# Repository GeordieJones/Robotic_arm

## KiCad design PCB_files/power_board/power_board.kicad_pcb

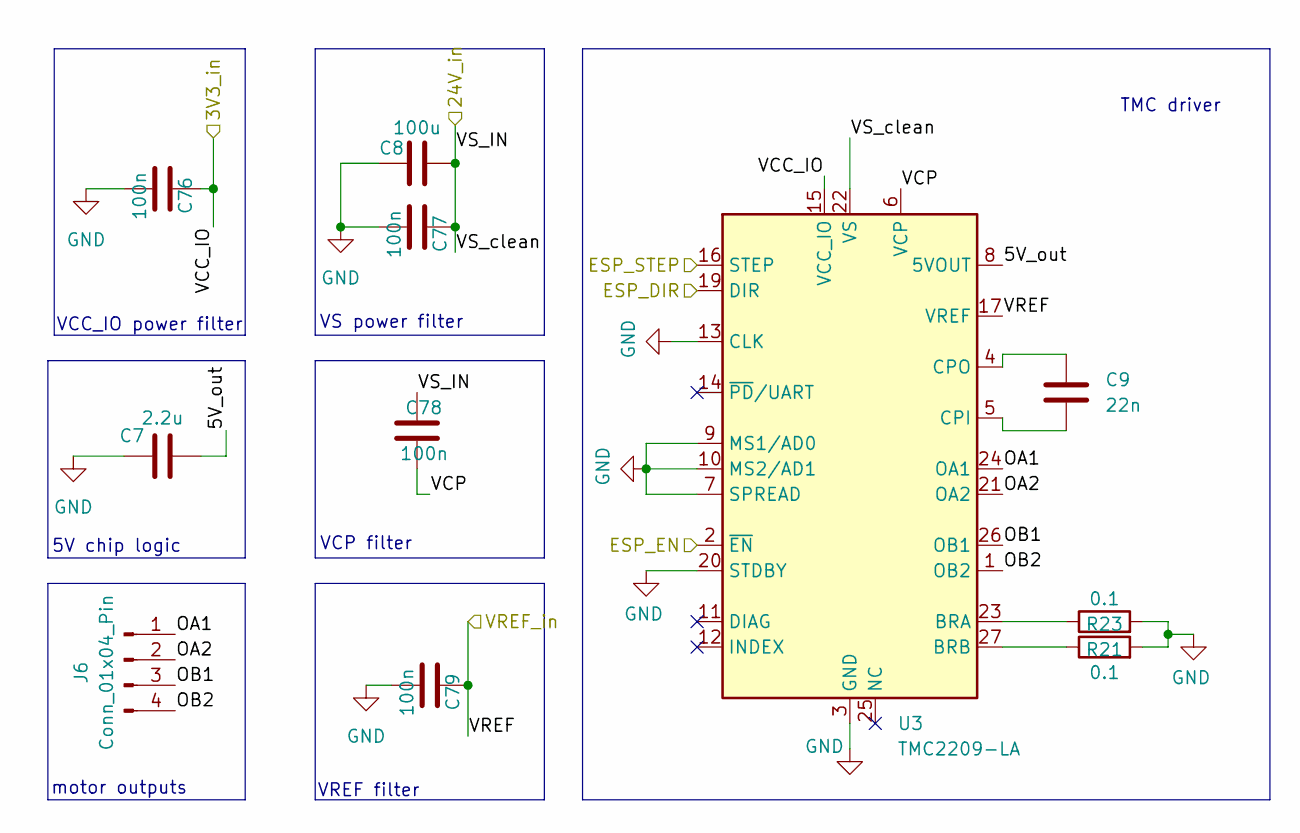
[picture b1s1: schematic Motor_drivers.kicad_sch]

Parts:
C7: 2.2u; C_0603_1608Metric
C8: 100u; CP_Radial_D6.3mm_P2.50mm
C9: 22n; C_0603_1608Metric
C76: 100n; C_0402_1005Metric; part samsung CL05B104KP5NNNC
C77, C78, C79: 100n; C_0603_1608Metric; part KEMET C0603C104K5RACTU
J6: Conn_01x04_Pin; JST_XA_B04B-XASK-1-A_1x04_P2.50mm_Vertical
R21, R23: 0.1; R_0805_2012Metric
U3: TMC2209-LA; VQFN-28-1EP_5x5mm_P0.5mm_EP3.7x3.7mm_ThermalVias

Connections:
3V3: C76.1, U3.15 (VCC_IO); also elsewhere on the board
24V: C8.1, C77.1, C78.1, U3.22 (VS), U3.28 (VS); also elsewhere on the board
/2_DIR: U3.19 (DIR); also elsewhere on the board
/2_STEP: U3.16 (STEP); also elsewhere on the board
/EN: U3.2 (~EN); also elsewhere on the board
/Motor_driver2/5V_out: C7.2, U3.8 (5VOUT)
/Motor_driver2/OA1: J6.1, U3.24 (OA1)
/Motor_driver2/OA2: J6.2, U3.21 (OA2)
/Motor_driver2/OB1: J6.3, U3.26 (OB1)
/Motor_driver2/OB2: J6.4, U3.1 (OB2)
/Motor_driver2/VCP: C78.2, U3.6 (VCP)
/VREF_ART2: C79.1, U3.17 (VREF); also elsewhere on the board
GND: C7.1, C8.2, C76.2, C77.2, C79.2, R21.2, R23.2, U3.3 (GND), U3.7 (SPREAD), U3.9 (MS1/AD0), U3.10 (MS2/AD1), U3.13 (CLK), U3.18 (GND), U3.20 (STDBY), U3.29 (GND); also elsewhere on the board
unnamed: R23.1, U3.23 (BRA)
unnamed: R21.1, U3.27 (BRB)
unnamed: C9.2, U3.5 (CPI)
unnamed: C9.1, U3.4 (CPO)

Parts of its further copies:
C4, C10, C13, C16, C19, C22: 2.2u; C_0603_1608Metric
C5, C11, C14, C17, C20, C23: 100u; CP_Radial_D6.3mm_P2.50mm
C6, C12, C15, C18, C21, C24: 22n; C_0603_1608Metric
C71, C80, C84, C91, C103, C107: 100n; C_0402_1005Metric; part samsung CL05B104KP5NNNC
C72, C73, C74, C81, C82, C83, C85, C86, C88, C97, C101, C102, C104, C105, C106, C108, C109, C110: 100n; C_0603_1608Metric; part KEMET C0603C104K5RACTU
J5, J8, J10, J11, J12, J13: Conn_01x04_Pin; JST_XA_B04B-XASK-1-A_1x04_P2.50mm_Vertical
R24, R25, R26, R27, R28, R29, R30, R36, R37, R38, R39, R40: 0.1; R_0805_2012Metric
U2, U4, U5, U6, U7, U10: TMC2209-LA; VQFN-28-1EP_5x5mm_P0.5mm_EP3.7x3.7mm_ThermalVias

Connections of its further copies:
3V3: C71.1, C80.1, C84.1, C91.1, C103.1, C107.1, U2.15 (VCC_IO), U4.15 (VCC_IO), U5.15 (VCC_IO), U6.15 (VCC_IO), U7.15 (VCC_IO), U10.15 (VCC_IO); also elsewhere on the board
24V: C5.1, C11.1, C14.1, C17.1, C20.1, C23.1, C72.1, C73.1, C81.1, C82.1, C85.1, C86.1, C97.1, C101.1, C104.1, C105.1, C108.1, C109.1, U2.22 (VS), U2.28 (VS), U4.22 (VS), U4.28 (VS), U5.22 (VS), U5.28 (VS), U6.22 (VS), U6.28 (VS), U7.22 (VS), U7.28 (VS), U10.22 (VS), U10.28 (VS); also elsewhere on the board
/1_DIR: U2.19 (DIR); also elsewhere on the board
/1_STEP: U2.16 (STEP); also elsewhere on the board
/3_DIR: U4.19 (DIR); also elsewhere on the board
/3_STEP: U4.16 (STEP); also elsewhere on the board
/4_DIR: U5.19 (DIR); also elsewhere on the board
/4_STEP: U5.16 (STEP); also elsewhere on the board
/5_DIR: U6.19 (DIR); also elsewhere on the board
/5_STEP: U6.16 (STEP); also elsewhere on the board
/6_DIR: U7.19 (DIR); also elsewhere on the board
/6_STEP: U7.16 (STEP); also elsewhere on the board
/7_DIR: U10.19 (DIR); also elsewhere on the board
/7_STEP: U10.16 (STEP); also elsewhere on the board
/EN: U2.2 (~EN), U4.2 (~EN), U5.2 (~EN), U6.2 (~EN), U7.2 (~EN), U10.2 (~EN); also elsewhere on the board
/Motor_driver1/5V_out: C4.2, U2.8 (5VOUT)
/Motor_driver1/OA1: J5.1, U2.24 (OA1)
/Motor_driver1/OA2: J5.2, U2.21 (OA2)
/Motor_driver1/OB1: J5.3, U2.26 (OB1)
/Motor_driver1/OB2: J5.4, U2.1 (OB2)
/Motor_driver1/VCP: C73.2, U2.6 (VCP)
/Motor_driver3/5V_out: C10.2, U4.8 (5VOUT)
/Motor_driver3/OA1: J8.1, U4.24 (OA1)
/Motor_driver3/OA2: J8.2, U4.21 (OA2)
/Motor_driver3/OB1: J8.3, U4.26 (OB1)
/Motor_driver3/OB2: J8.4, U4.1 (OB2)
/Motor_driver3/VCP: C82.2, U4.6 (VCP)
/Motor_driver4/5V_out: C13.2, U5.8 (5VOUT)
/Motor_driver4/OA1: J10.1, U5.24 (OA1)
/Motor_driver4/OA2: J10.2, U5.21 (OA2)
/Motor_driver4/OB1: J10.3, U5.26 (OB1)
/Motor_driver4/OB2: J10.4, U5.1 (OB2)
/Motor_driver4/VCP: C86.2, U5.6 (VCP)
/Motor_driver5/5V_out: C16.2, U6.8 (5VOUT)
/Motor_driver5/OA1: J11.1, U6.24 (OA1)
/Motor_driver5/OA2: J11.2, U6.21 (OA2)
/Motor_driver5/OB1: J11.3, U6.26 (OB1)
/Motor_driver5/OB2: J11.4, U6.1 (OB2)
/Motor_driver5/VCP: C101.2, U6.6 (VCP)
/Motor_driver6/5V_out: C19.2, U7.8 (5VOUT)
/Motor_driver6/OA1: J12.1, U7.24 (OA1)
/Motor_driver6/OA2: J12.2, U7.21 (OA2)
/Motor_driver6/OB1: J12.3, U7.26 (OB1)
/Motor_driver6/OB2: J12.4, U7.1 (OB2)
/Motor_driver6/VCP: C105.2, U7.6 (VCP)
/Motor_driver7/5V_out: C22.2, U10.8 (5VOUT)
/Motor_driver7/OA1: J13.1, U10.24 (OA1)
/Motor_driver7/OA2: J13.2, U10.21 (OA2)
/Motor_driver7/OB1: J13.3, U10.26 (OB1)
/Motor_driver7/OB2: J13.4, U10.1 (OB2)
/Motor_driver7/VCP: C109.2, U10.6 (VCP)
/VREF_ART1: C74.1, U2.17 (VREF); also elsewhere on the board
/VREF_ART2: C83.1, U4.17 (VREF); also elsewhere on the board
/VREF_ART3: C88.1, C102.1, C106.1, C110.1, U5.17 (VREF), U6.17 (VREF), U7.17 (VREF), U10.17 (VREF); also elsewhere on the board
GND: C4.1, C5.2, C10.1, C11.2, C13.1, C14.2, C16.1, C17.2, C19.1, C20.2, C22.1, C23.2, C71.2, C72.2, C74.2, C80.2, C81.2, C83.2, C84.2, C85.2, C88.2, C91.2, C97.2, C102.2, C103.2, C104.2, C106.2, C107.2, C108.2, C110.2, R24.2, R25.2, R26.2, R27.2, R28.2, R29.2, R30.2, R36.2, R37.2, R38.2, R39.2, R40.2, U2.3 (GND), U2.7 (SPREAD), U2.9 (MS1/AD0), U2.10 (MS2/AD1), U2.13 (CLK), U2.18 (GND), U2.20 (STDBY), U2.29 (GND), U4.3 (GND), U4.7 (SPREAD), U4.9 (MS1/AD0), U4.10 (MS2/AD1), U4.13 (CLK), U4.18 (GND), U4.20 (STDBY), U4.29 (GND), U5.3 (GND), U5.7 (SPREAD), U5.9 (MS1/AD0), U5.10 (MS2/AD1), U5.13 (CLK), U5.18 (GND), U5.20 (STDBY), U5.29 (GND), U6.3 (GND), U6.7 (SPREAD), U6.9 (MS1/AD0), U6.10 (MS2/AD1), U6.13 (CLK), U6.18 (GND), U6.20 (STDBY), U6.29 (GND), U7.3 (GND), U7.7 (SPREAD), U7.9 (MS1/AD0), U7.10 (MS2/AD1), U7.13 (CLK), U7.18 (GND), U7.20 (STDBY), U7.29 (GND), U10.3 (GND), U10.7 (SPREAD), U10.9 (MS1/AD0), U10.10 (MS2/AD1), U10.13 (CLK), U10.18 (GND), U10.20 (STDBY), U10.29 (GND); also elsewhere on the board
unnamed: R25.1, U2.23 (BRA)
unnamed: R24.1, U2.27 (BRB)
unnamed: C6.2, U2.5 (CPI)
unnamed: C6.1, U2.4 (CPO)
unnamed: R27.1, U4.23 (BRA)
unnamed: R26.1, U4.27 (BRB)
unnamed: C12.2, U4.5 (CPI)
unnamed: C12.1, U4.4 (CPO)
unnamed: R28.1, U5.23 (BRA)
unnamed: R37.1, U5.27 (BRB)
unnamed: C15.2, U5.5 (CPI)
unnamed: C15.1, U5.4 (CPO)
unnamed: R29.1, U6.23 (BRA)
unnamed: R38.1, U6.27 (BRB)
unnamed: C18.2, U6.5 (CPI)
unnamed: C18.1, U6.4 (CPO)
unnamed: R30.1, U7.23 (BRA)
unnamed: R39.1, U7.27 (BRB)
unnamed: C21.2, U7.5 (CPI)
unnamed: C21.1, U7.4 (CPO)
unnamed: R36.1, U10.23 (BRA)
unnamed: R40.1, U10.27 (BRB)
unnamed: C24.2, U10.5 (CPI)
unnamed: C24.1, U10.4 (CPO)

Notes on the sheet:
VS power filter
VCP filter
VREF filter
TMC driver
VCC_IO power filter
motor outputs
5V chip logic

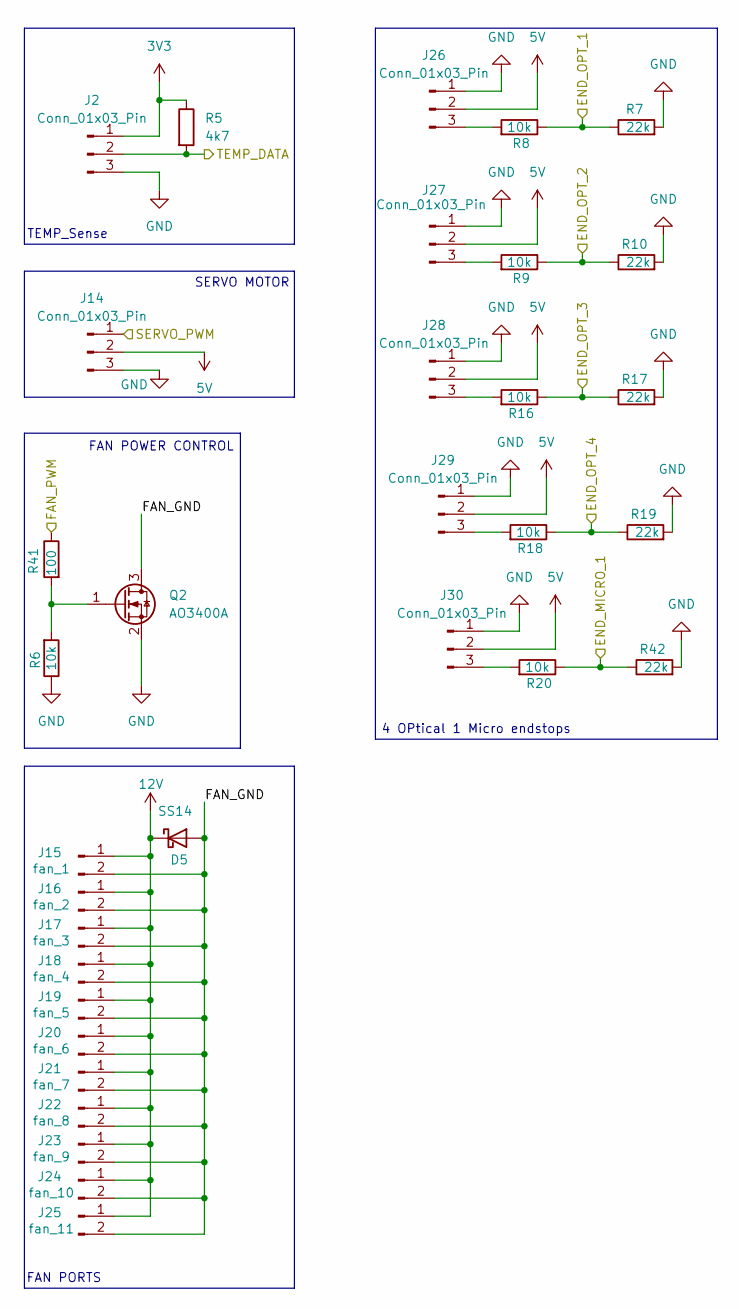
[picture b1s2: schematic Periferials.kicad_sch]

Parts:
D5: SS14; D_SMA
J2, J26, J27, J28, J29, J30: Conn_01x03_Pin; JST_XH_B3B-XH-A_1x03_P2.50mm_Vertical
J14: Conn_01x03_Pin; PinHeader_1x03_P2.54mm_Vertical
J15: fan_1; PinSocket_1x02_P2.54mm_Vertical
J16: fan_2; PinSocket_1x02_P2.54mm_Vertical
J17: fan_3; PinSocket_1x02_P2.54mm_Vertical
J18: fan_4; PinSocket_1x02_P2.54mm_Vertical
J19: fan_5; PinSocket_1x02_P2.54mm_Vertical
J20: fan_6; PinSocket_1x02_P2.54mm_Vertical
J21: fan_7; PinSocket_1x02_P2.54mm_Vertical
J22: fan_8; PinSocket_1x02_P2.54mm_Vertical
J23: fan_9; PinSocket_1x02_P2.54mm_Vertical
J24: fan_10; PinSocket_1x02_P2.54mm_Vertical
J25: fan_11; PinSocket_1x02_P2.54mm_Vertical
Q2: AO3400A; SOT-23
R5: 4k7; R_0402_1005Metric
R6, R8, R9, R16, R18, R20: 10k; R_1206_3216Metric
R7, R10, R17, R19, R42: 22k; R_0603_1608Metric
R41: 100; R_0402_1005Metric; part YAGEO RC0402FR-07100RL

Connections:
3V3: J2.1, R5.1; also elsewhere on the board
5V: J14.2, J26.2, J27.2, J28.2, J29.2, J30.2; also elsewhere on the board
12V: D5.1 (K), J15.1, J16.1, J17.1, J18.1, J19.1, J20.1, J21.1, J22.1, J23.1, J24.1, J25.1; also elsewhere on the board
/FAN_PWM: R41.1; also elsewhere on the board
/MICRO_END1: R20.1, R42.1; also elsewhere on the board
/OPT_END1: R7.1, R8.1; also elsewhere on the board
/OPT_END2: R9.1, R10.1; also elsewhere on the board
/OPT_END3: R16.1, R17.1; also elsewhere on the board
/OPT_END4: R18.1, R19.1; also elsewhere on the board
/Periferials/FAN_GND: D5.2 (A), J15.2, J16.2, J17.2, J18.2, J19.2, J20.2, J21.2, J22.2, J23.2, J24.2, J25.2, Q2.3 (D)
/SERVO_PWM: J14.1; also elsewhere on the board
/TEMP_DATA: J2.2, R5.2; also elsewhere on the board
GND: J2.3, J14.3, J26.1, J27.1, J28.1, J29.1, J30.1, Q2.2 (S), R6.1, R7.2, R10.2, R17.2, R19.2, R42.2; also elsewhere on the board
unnamed: J26.3, R8.2
unnamed: J27.3, R9.2
unnamed: J28.3, R16.2
unnamed: J29.3, R18.2
unnamed: J30.3, R20.2
unnamed: Q2.1 (G), R6.2, R41.2

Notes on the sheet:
FAN PORTS
FAN POWER CONTROL
SERVO MOTOR
TEMP_Sense
4 OPtical 1 Micro endstops

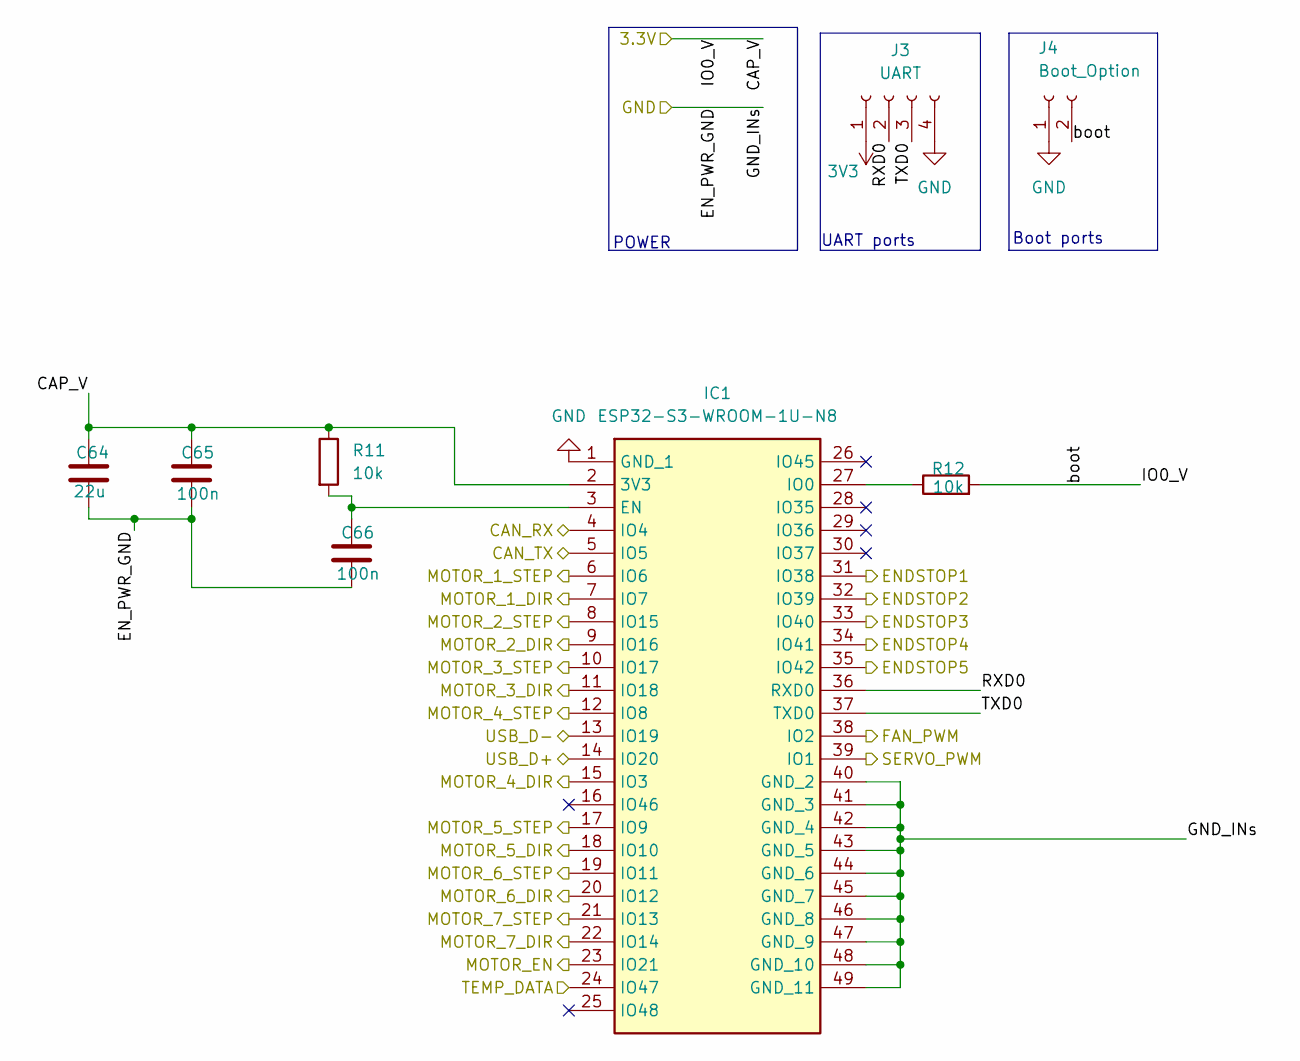
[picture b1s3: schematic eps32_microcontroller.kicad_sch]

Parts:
C64: 22u; C_0402_1005Metric; part Murata Electronics GRM158R61A226ME15D
C65, C66: 100n; C_0402_1005Metric; part samsung CL05B104KP5NNNC
IC1: ESP32-S3-WROOM-1U-N8; ESP32S3WROOM1UN8; Manufacturer_Part_Number ESP32-S3-WROOM-1U-N8; Mouser Part Number 356-ESP32S3WROOM1UN8
J3: UART; PinSocket_1x04_P2.54mm_Vertical
J4: Boot_Option; PinSocket_1x02_P2.00mm_Vertical
R11, R12: 10k; R_0402_1005Metric; part number Samsung Electro-Mechanics RC1005F103CS

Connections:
3V3: C64.1, C65.1, IC1.2 (3V3), J3.1, J4.2, R11.1, R12.2; also elsewhere on the board
/1_DIR: IC1.7 (IO7); also elsewhere on the board
/1_STEP: IC1.6 (IO6); also elsewhere on the board
/2_DIR: IC1.9 (IO16); also elsewhere on the board
/2_STEP: IC1.8 (IO15); also elsewhere on the board
/3_DIR: IC1.11 (IO18); also elsewhere on the board
/3_STEP: IC1.10 (IO17); also elsewhere on the board
/4_DIR: IC1.15 (IO3); also elsewhere on the board
/4_STEP: IC1.12 (IO8); also elsewhere on the board
/5_DIR: IC1.18 (IO10); also elsewhere on the board
/5_STEP: IC1.17 (IO9); also elsewhere on the board
/6_DIR: IC1.20 (IO12); also elsewhere on the board
/6_STEP: IC1.19 (IO11); also elsewhere on the board
/7_DIR: IC1.22 (IO14); also elsewhere on the board
/7_STEP: IC1.21 (IO13); also elsewhere on the board
/C_RX: IC1.4 (IO4); also elsewhere on the board
/C_TX: IC1.5 (IO5); also elsewhere on the board
/EN: IC1.23 (IO21); also elsewhere on the board
/FAN_PWM: IC1.38 (IO2); also elsewhere on the board
/MICRO_END1: IC1.35 (IO42); also elsewhere on the board
/OPT_END1: IC1.31 (IO38); also elsewhere on the board
/OPT_END2: IC1.32 (IO39); also elsewhere on the board
/OPT_END3: IC1.33 (IO40); also elsewhere on the board
/OPT_END4: IC1.34 (IO41); also elsewhere on the board
/SERVO_PWM: IC1.39 (IO1); also elsewhere on the board
/TEMP_DATA: IC1.24 (IO47); also elsewhere on the board
/USB+: IC1.14 (IO20); also elsewhere on the board
/USB-: IC1.13 (IO19); also elsewhere on the board
/esp32_microcontroller/RXD0: IC1.36 (RXD0), J3.2
/esp32_microcontroller/TXD0: IC1.37 (TXD0), J3.3
GND: C64.2, C65.2, C66.2, IC1.1 (GND_1), IC1.40 (GND_2), IC1.41 (GND_3), IC1.42 (GND_4), IC1.43 (GND_5), IC1.44 (GND_6), IC1.45 (GND_7), IC1.46 (GND_8), IC1.47 (GND_9), IC1.48 (GND_10), IC1.49 (GND_11), J3.4, J4.1; also elsewhere on the board
unnamed: C66.1, IC1.3 (EN), R11.2
unnamed: IC1.27 (IO0), R12.1

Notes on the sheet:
UART ports
POWER
Boot ports

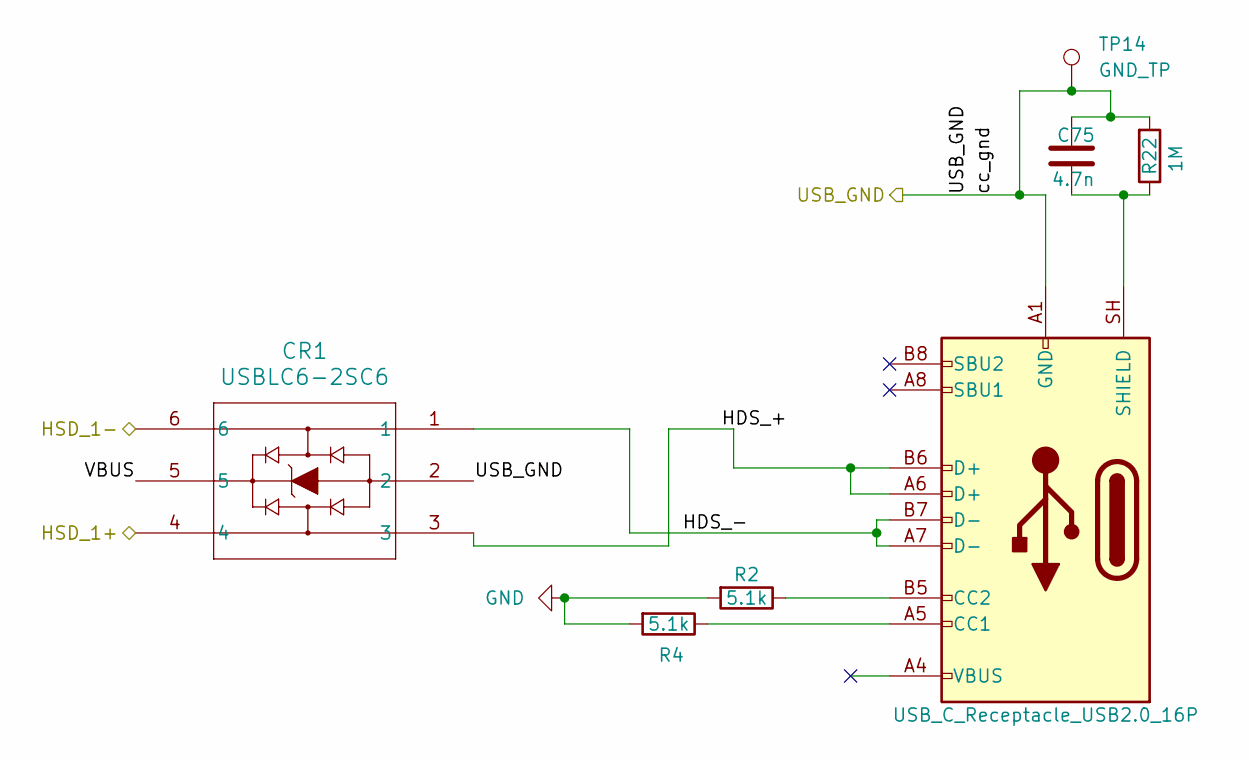
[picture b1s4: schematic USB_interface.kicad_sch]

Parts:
C75: 4.7n; LED_0603_1608Metric
CR1: USBLC6-2SC6; SOT23-6L_STM-M
J7: USB_C_Receptacle_USB2.0_16P; USB_C_Receptacle_GCT_USB4105-xx-A_16P_TopMnt_Horizontal; part USB4105-GF-A
R2, R4: 5.1k; R_0402_1005Metric
R22: 1M; R_0402_1005Metric; part number YAGEO RC0402FR-071ML
TP14: GND_TP; Pin_D1.0mm_L10.0mm

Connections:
/USB+: CR1.4; also elsewhere on the board
/USB-: CR1.6; also elsewhere on the board
/USB_interface/HDS_+: CR1.3, J7.A6 (D+), J7.B6 (D+)
/USB_interface/HDS_-: CR1.1, J7.A7 (D-), J7.B7 (D-)
/USB_interface/VBUS: CR1.5
GND: C75.1, CR1.2, J7.A1 (GND), J7.A12 (GND), J7.B1 (GND), J7.B12 (GND), R2.2, R4.2, R22.2, TP14.1 (1_1); also elsewhere on the board
unnamed: J7.A5 (CC1), R4.1
unnamed: J7.B5 (CC2), R2.1
unnamed: C75.2, J7.SH (SHIELD), R22.1

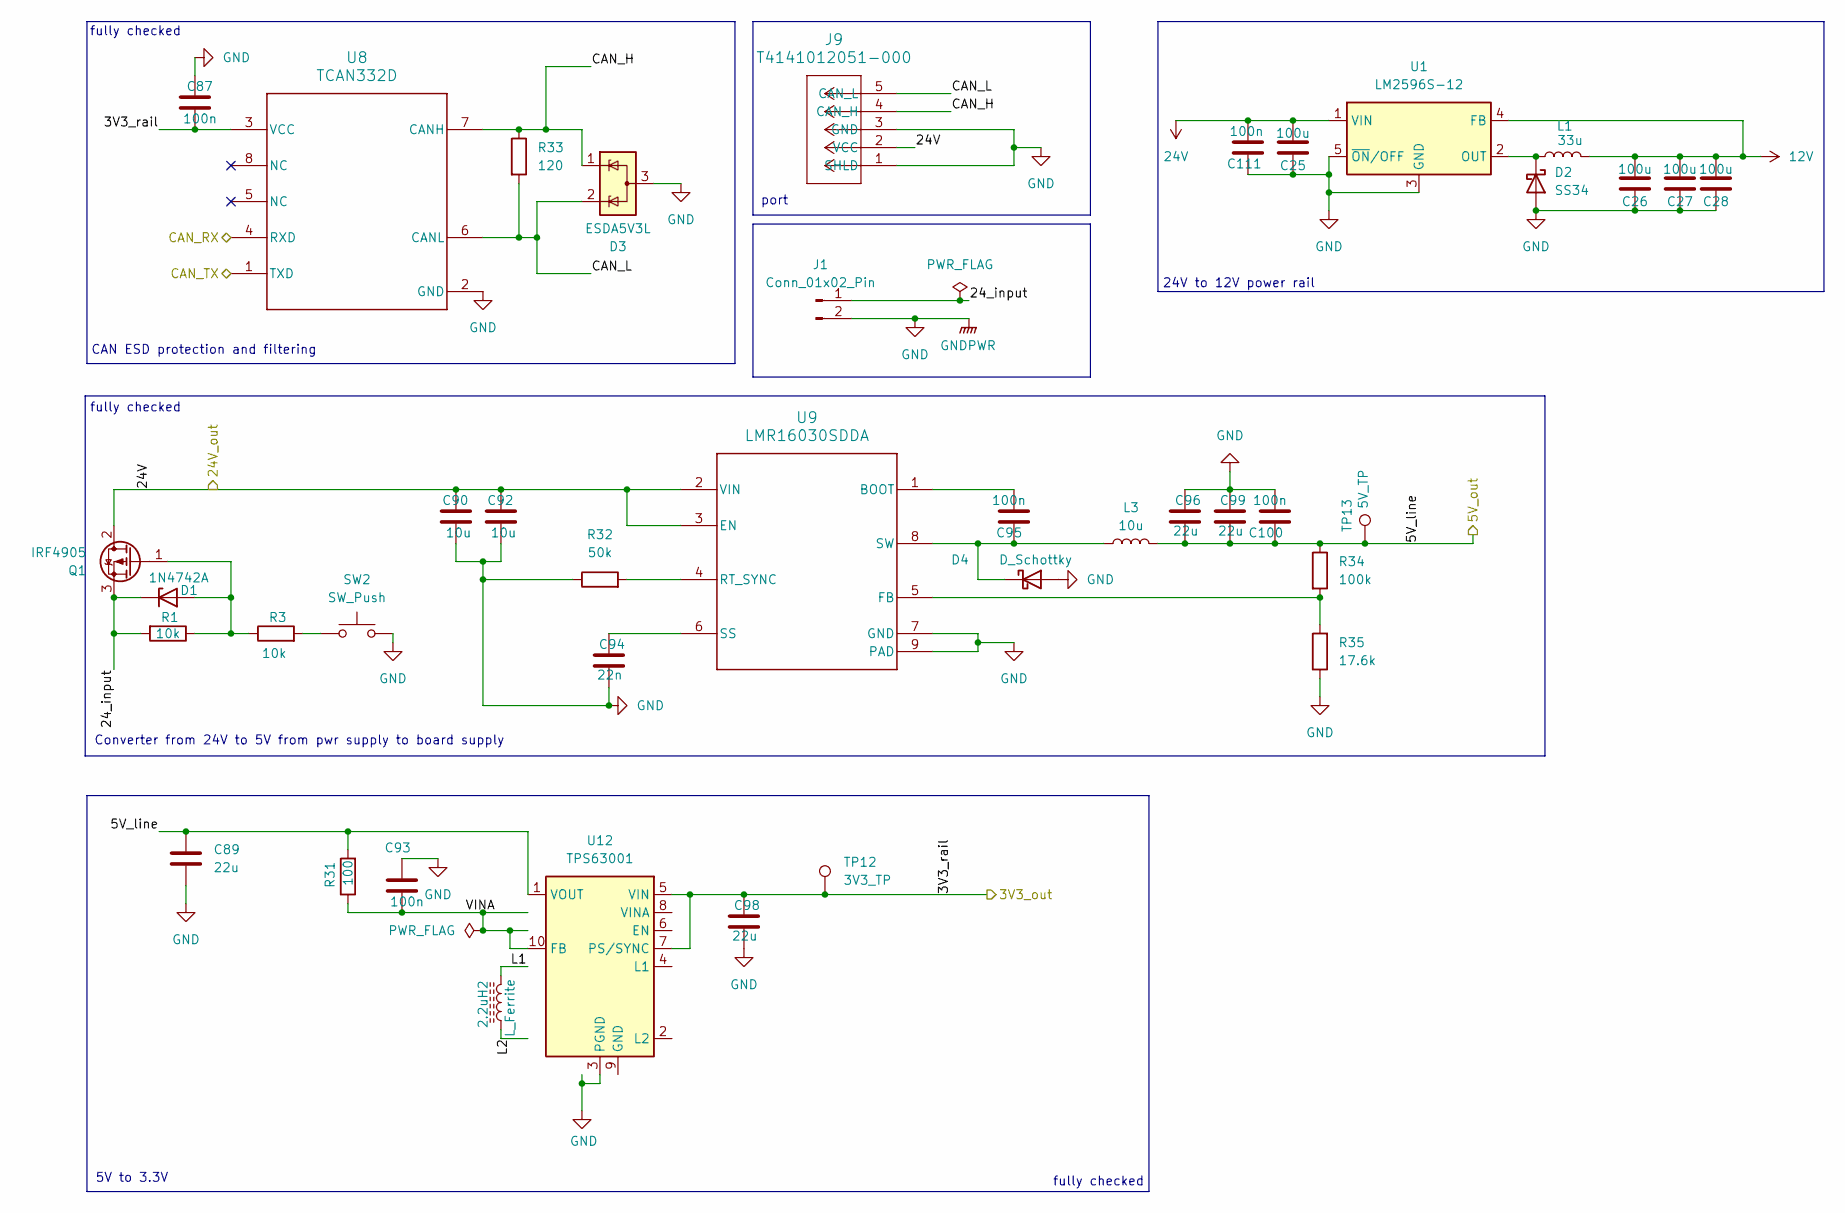
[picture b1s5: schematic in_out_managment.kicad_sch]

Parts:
2.2uH2: L_Ferrite; L_0402_1005Metric; part number BLM15PX601SN1D
C25, C26, C27, C28: 100u; CP_Radial_D6.3mm_P2.50mm
C87, C93, C95, C100: 100n; C_0402_1005Metric; part samsung CL05B104KP5NNNC
C89, C96, C98, C99: 22u; C_0402_1005Metric; part Murata Electronics GRM158R61A226ME15D
C90, C92: 10u; C_0805_2012Metric; part 0805W106K500CC
C94: 22n; C_0402_1005Metric; part Murata Electronics GRM155R71H223KA12D
C111: 100n; C_0603_1608Metric; part KEMET C0603C104K5RACTU
D1: 1N4742A; D_DO-41_SOD81_P10.16mm_Horizontal
D2: SS34; D_SMA
D3: ESDA5V3L; SOT-23-3
D4: D_Schottky; D_SMA
J1: Conn_01x02_Pin; AMASS_XT60PW-M_1x02_P7.20mm_Horizontal
J9: T4141012051-000; CONN5_T4141012051
L1: 33u; L_12x12mm_H8mm
L3: 10u; L_0805_2012Metric
Q1: IRF4905; TO-220-3_Vertical
R1, R3: 10k; R_1206_3216Metric
R31: 100; R_0402_1005Metric; part YAGEO RC0402FR-07100RL
R32: 50k; R_0603_1608Metric
R33: 120; R_0402_1005Metric
R34: 100k; R_0402_1005Metric; part number YAGEO RC0402FR-07100KL
R35: 17.6k; R_0603_1608Metric
SW2: SW_Push; SW_PUSH_6mm_H9.5mm
TP12: 3V3_TP; Pin_D1.0mm_L10.0mm
TP13: 5V_TP; Pin_D1.0mm_L10.0mm
U1: LM2596S-12; TO-263-5_TabPin3
U8: TCAN332D; D0008A_N
U9: LMR16030SDDA; DDA0008E_M
U12: TPS63001; Texas_DRC0010J_ThermalVias

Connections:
3V3: C87.2, C98.1, TP12.1 (1_1), U8.3 (VCC), U12.5 (VIN), U12.7 (PS/SYNC); also elsewhere on the board
5V: C89.1, C96.2, C99.2, C100.1, L3.2, R31.2, R34.1, TP13.1 (1_1), U12.1 (VOUT); also elsewhere on the board
12V: C26.1, C27.1, C28.1, L1.2, U1.4 (FB); also elsewhere on the board
24V: C25.1, C90.1, C92.1, C111.2, J9.2 (VCC), Q1.2 (D), U1.1 (VIN), U9.2 (VIN), U9.3 (EN); also elsewhere on the board
/C_RX: U8.4 (RXD); also elsewhere on the board
/C_TX: U8.1 (TXD); also elsewhere on the board
/in_out_managment/24_input: D1.1 (K), J1.1, Q1.3 (S), R1.2
/in_out_managment/CAN_H: D3.1 (K), J9.4 (CAN_H), R33.1, U8.7 (CANH)
/in_out_managment/CAN_L: D3.2 (K), J9.5 (CAN_L), R33.2, U8.6 (CANL)
/in_out_managment/L1: 2.2uH2.2
/in_out_managment/L2: 2.2uH2.1
/in_out_managment/VINA: C93.2, R31.1, U12.10 (FB)
GND: C25.2, C26.2, C27.2, C28.2, C87.1, C89.2, C90.2, C92.2, C93.1, C94.2, C96.1, C98.2, C99.1, C100.2, C111.1, D2.2 (A), D3.3 (A), D4.2 (A), J1.2, J9.1 (SHLD), J9.3 (GND), R32.1, R35.1, SW2.2, U1.3 (GND), U1.5 (~ON/OFF), U8.2 (GND), U9.7 (GND), U9.9 (PAD), U12.3 (PGND), U12.11 (PGND); also elsewhere on the board
unnamed: D1.2 (A), Q1.1 (G), R1.1, R3.1
unnamed: D2.1 (K), L1.1, U1.2 (OUT)
unnamed: C95.1, D4.1 (K), L3.1, U9.8 (SW)
unnamed: R3.2, SW2.1
unnamed: C95.2, U9.1 (BOOT)
unnamed: R34.2, R35.2, U9.5 (FB)
unnamed: R32.2, U9.4 (RT_SYNC)
unnamed: C94.1, U9.6 (SS)

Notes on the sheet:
24V to 12V power rail
CAN ESD protection and filtering
fully checked
port
Converter from 24V to 5V from pwr supply to board supply
5V to 3.3V

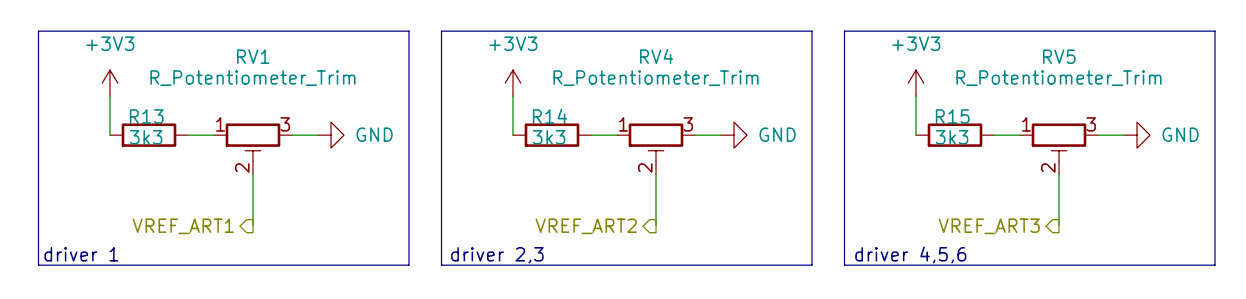
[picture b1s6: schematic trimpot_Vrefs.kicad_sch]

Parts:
R13, R14, R15: 3k3; R_0402_1005Metric; part number YAGEO RC0402FR-073K3L
RV1, RV4, RV5: R_Potentiometer_Trim; Potentiometer_Bourns_3314J_Vertical

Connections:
+3V3: R13.2, R14.2, R15.2
/VREF_ART1: RV1.2; also elsewhere on the board
/VREF_ART2: RV4.2; also elsewhere on the board
/VREF_ART3: RV5.2; also elsewhere on the board
GND: RV1.3, RV4.3, RV5.3; also elsewhere on the board
unnamed: R13.1, RV1.1
unnamed: R14.1, RV4.1
unnamed: R15.1, RV5.1

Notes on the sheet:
driver 4,5,6
driver 1
driver 2,3

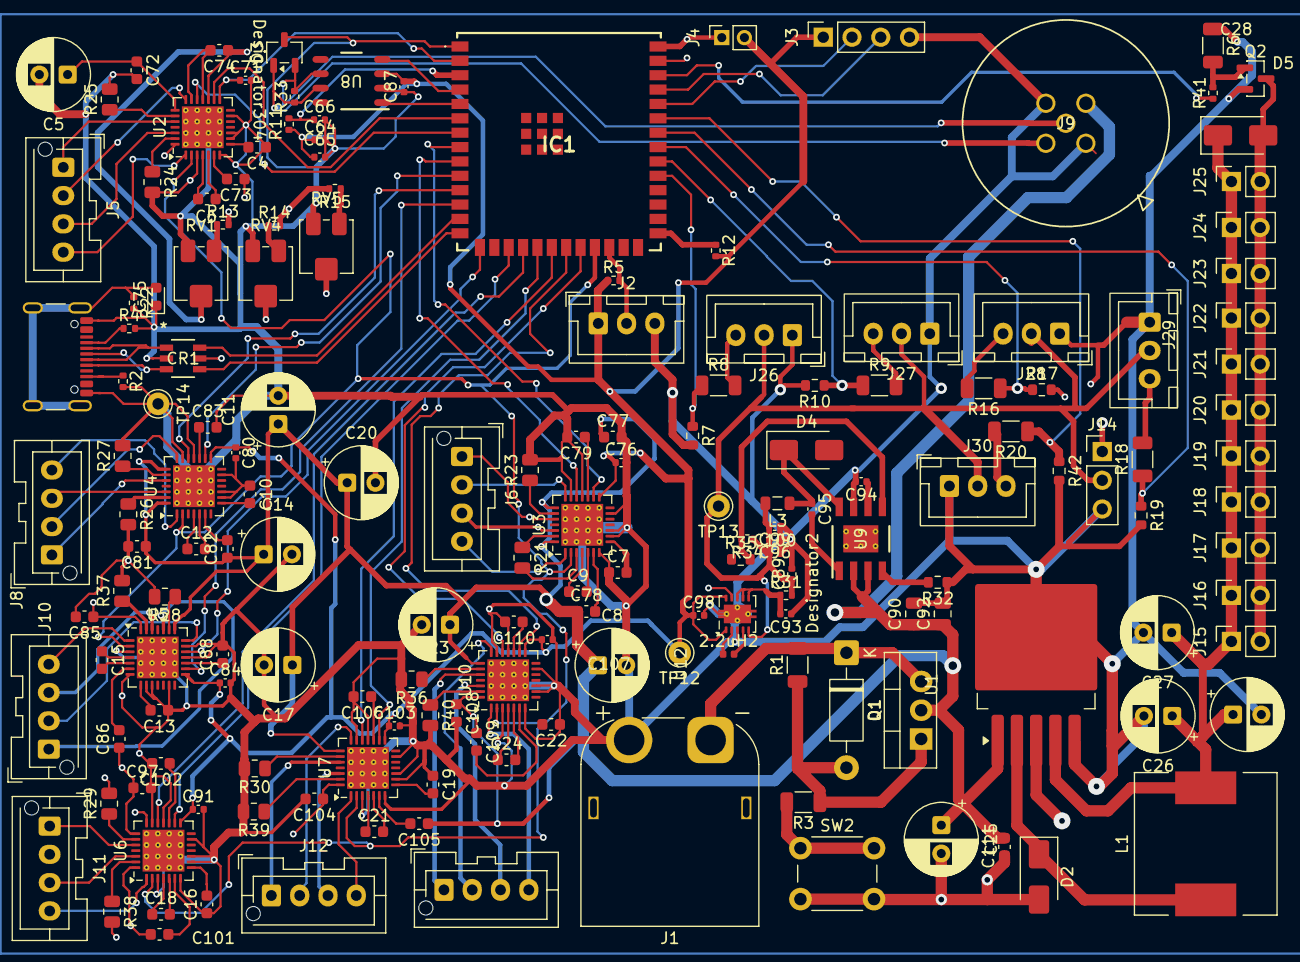
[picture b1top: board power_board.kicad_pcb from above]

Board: 2 copper layers, 171 parts (0 on the bottom side), 137 nets.
